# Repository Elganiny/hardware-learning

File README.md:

# Hardware learning log: PCB design with KiCad

Small boards I design while teaching myself electronics and PCB design in **KiCad 10**, with robotics in mind. Each project uses only what I had learned at that point, and the next one builds on it, so the repo shows the progress from my first schematic to complete microcontroller boards.

Every project folder has the KiCad files, a PDF of the schematic, 3D renders, a BOM, the automatic check results and a README that explains **what I decided and why**.

## Projects

| # | Project | What's new in it | Status | |
|---|---|---|---|---|
| P00 | [Mini-Dashboard V1](projects/P00-mini-dashboard-v1/) | first schematic and PCB: LED with series resistor, button with pull-up, JST connector, GND zone | designed, ERC/DRC clean |  |
| P01 | [Mini-Dashboard V2](projects/P01-mini-dashboard-v2/) | its own power supply: micro-USB 5 V → NCP1117 linear regulator → 3.3 V, heat calculation, decoupling placement | designed, ERC/DRC clean |  |
| P02 | Mini-Dashboard V3 (planned) | its own RP2040 microcontroller: flash, crystal, USB data | planned | |

"Designed" means schematic and PCB are finished and pass KiCad's checks. Boards that were manufactured and tested will say so, with measurements.

Units without their own board are written up in the [learning log](learning-log/).

## How I work

1. Learn one topic from a complete, documented design (currently Raspberry Pi's *Hardware design with RP2040*).
2. Design a small board that uses it, following a fixed order of work with checks between the steps: schematic → ERC and reading the netlist → footprints → board outline and connectors → placement → net classes → routing → DRC with schematic parity → labels.
3. Review it against a checklist and write down what I would do differently. Those lessons are in each project's README and CHANGELOG.

## Repository layout

```
projects/<Pnn-name>/
  kicad/      KiCad 10 project (.kicad_pro, .kicad_sch, .kicad_pcb)
  docs/       schematic.pdf, pcb_top.png, pcb_bottom.png, bom.csv, checks.md (generated)
  README.md   what, why, design decisions, status, known issues, test plan
  CHANGELOG.md
templates/    README and CHANGELOG templates for new projects
tools/        update_docs.py: copies the latest KiCad files in and regenerates docs/
```

Regenerate the docs after a change (needs KiCad 10 installed):

```
python tools/update_docs.py
```

## Licence

Copyright 2026 Mohammed Elganayni.

The hardware designs in this repository are licensed under the **CERN Open Hardware Licence Version 2 – Permissive** (SPDX: `CERN-OHL-P-2.0`), see [LICENSE](LICENSE). You may use, modify, manufacture and distribute them; please keep the copyright and licence notice.

KiCad's standard symbol and footprint libraries and the manufacturers' datasheets referenced here have their own terms.

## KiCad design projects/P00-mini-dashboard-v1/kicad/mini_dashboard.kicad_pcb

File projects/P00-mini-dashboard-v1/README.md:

# P00 · Mini-Dashboard V1

My first schematic and PCB: a tiny board with a **power LED** and a **push button**, connected to a microcontroller board by a 3-pin JST PH cable. The microcontroller board supplies the 3.3 V.

| Top | Bottom |
|---|---|
|  |  |

| | |
|---|---|
| Board | 25 × 20 mm, 2 copper layers, parts on top |
| Parts | 5 (LED, 2 resistors, button, connector) |
| Checks | see [docs/checks.md](docs/checks.md): ERC 0 / 0, DRC 0 / 0 with schematic parity |
| Files | [schematic PDF](docs/schematic.pdf) · [BOM](docs/bom.csv) · [KiCad project](kicad/) |
| Status | designed, **not manufactured, not tested** |

## Interface

| J1 pin (JST PH, 2.0 mm) | Signal | Direction |
|---|---|---|
| 1 | GND | — |
| 2 | +3.3 V | in, from the MCU board |
| 3 | BTN | out: 3.3 V = released, 0 V = pressed |

## Design decisions

| Decision | Why |
|---|---|
| **R1 = 270 Ω** in series with a red LED | the LED takes about 2.0 V, the resistor the remaining 1.3 V: I = 1.3 V / 270 Ω ≈ **4.8 mA**, enough for an indicator. Resistor power 6.3 mW |
| **Button to GND with a 10 kΩ pull-up (R2) on the board** | released → R2 pulls BTN to 3.3 V, pressed → 0 V. On the board so it works with any MCU, even if the firmware forgets its internal pull-up. Current while pressed: 0.33 mA |
| **No 100 nF capacitor** | there is no chip on the board, so nothing draws fast current bursts |
| **0603 SMD parts, 6 mm through-hole button** | 0603 is still comfortable to hand-solder; the through-hole button survives being pressed |
| **PWR_FLAG on +3.3 V and GND** | power enters through the connector's passive pins, so ERC needs to be told the nets are powered from outside |
| **GND zone on the bottom layer** | through-hole GND pads connect to it directly; less routing |
| **Trace between the button's two pads "1"** | the button connects them internally, but KiCad's DRC treats them as separate pads |

## Known issues / what I'd do differently

- Traces are long (about 100 mm in total) because I routed before the placement was final.
- All traces are 0.2 mm; power traces should be wider by habit (V2 uses net widths of 0.4 mm).
- No mounting holes, no labels for the connector pins, no board name or version on the silkscreen.
- Values are partly the symbol's placeholders (`LED`, `SW_Push`), so the BOM doesn't say exactly what to order.

These were addressed in [P01](../P01-mini-dashboard-v2/) where possible.

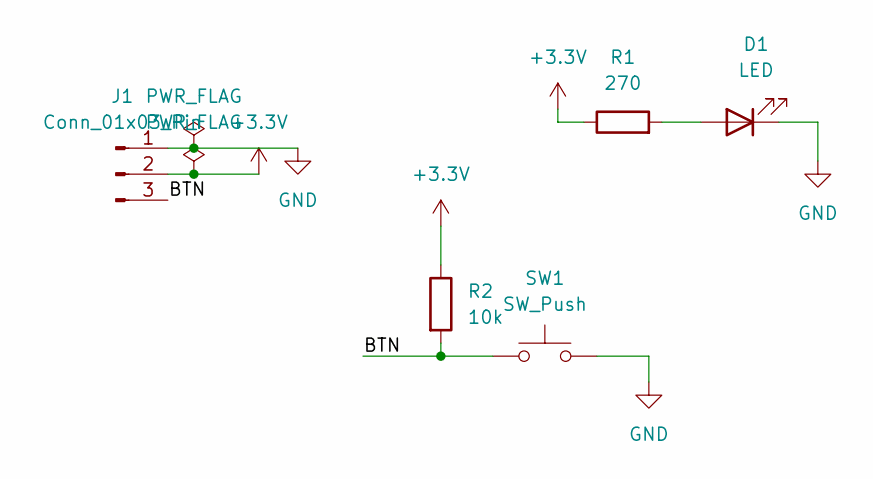
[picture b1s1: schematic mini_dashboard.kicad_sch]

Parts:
D1: LED; LED_0603_1608Metric
J1: Conn_01x03_Pin; JST_PH_B3B-PH-K_1x03_P2.00mm_Vertical
R1: 270; R_0603_1608Metric
R2: 10k; R_0603_1608Metric
SW1: SW_Push; SW_PUSH_6mm

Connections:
+3.3V: J1.2, R1.1, R2.1
/BTN: J1.3, R2.2, SW1.1
GND: D1.1 (K), J1.1, SW1.2
unnamed: D1.2 (A), R1.2

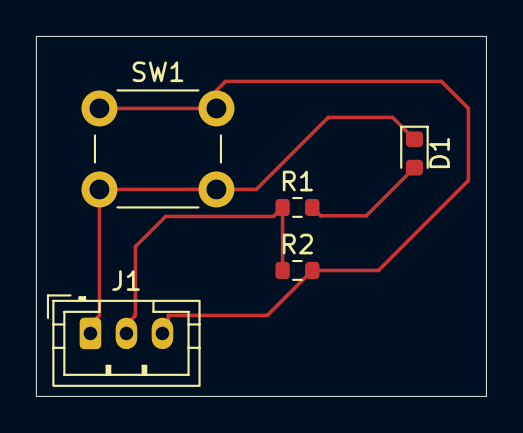
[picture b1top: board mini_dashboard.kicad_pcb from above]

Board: 2 copper layers, 25.0 x 20.0 mm, 5 parts (0 on the bottom side), 4 nets.

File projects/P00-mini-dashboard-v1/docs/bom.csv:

"Refs","Value","Footprint","Qty","DNP"
"D1","LED","LED_SMD:LED_0603_1608Metric","1",""
"J1","Conn_01x03_Pin","Connector_JST:JST_PH_B3B-PH-K_1x03_P2.00mm_Vertical","1",""
"R1","270","Resistor_SMD:R_0603_1608Metric","1",""
"R2","10k","Resistor_SMD:R_0603_1608Metric","1",""
"SW1","SW_Push","Button_Switch_THT:SW_PUSH_6mm","1",""

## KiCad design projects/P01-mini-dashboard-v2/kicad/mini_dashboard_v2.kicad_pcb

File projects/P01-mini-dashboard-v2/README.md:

# P01 · Mini-Dashboard V2: its own power supply

V1 needed 3.3 V from another board. **V2 makes its own 3.3 V from USB**: a micro-USB socket brings 5 V, an NCP1117 linear regulator turns it into 3.3 V, and the LED and button from V1 stay. Plug it into any USB charger and the LED shows that the regulator works.

| Top | Bottom |
|---|---|
|  |  |

| | |
|---|---|
| Board | 25 × 23 mm, 2 copper layers, parts on top |
| Parts | 9 (regulator, 2 capacitors, LED, 2 resistors, button, 2 connectors) |
| Checks | see [docs/checks.md](docs/checks.md): ERC 0 / 0, DRC 0 / 0 with schematic parity |
| Files | [schematic PDF](docs/schematic.pdf) · [BOM](docs/bom.csv) · [KiCad project](kicad/) |
| Status | designed, **not manufactured, not tested** |

## Interfaces

| Connector | Pin | Signal | Note |
|---|---|---|---|
| J2 micro-USB (Amphenol 10118194-0001LF) | VBUS | 5 V in | power only |
| | D+, D−, ID | — | not connected (no USB data on this board) |
| | GND, shield | GND | |
| J1 JST PH, 2.0 mm | 1 | GND | |
| | 2 | **+3.3 V out**, max 100 mA | the other board must not have its own 3.3 V regulator on this pin |
| | 3 | BTN | 3.3 V released, 0 V pressed |

## Design decisions

| Decision | Why |
|---|---|
| **NCP1117 3.3 V linear regulator** | simple, needs only two capacitors. Its dropout is at most 1.10 V at 100 mA, so it needs ≥ 4.4 V in; USB gives 5 V |
| **10 µF 16 V X5R (0805) on the input and output** | the datasheet uses 10 µF in and out; the output capacitor is part of the regulator's control loop and keeps it stable. 16 V is more than 3× the 5 V it sees |
| **Heat check** | the board draws about 5 mA: (5.0 − 3.3) V × 5 mA = 9 mW → +1.4 °C at 160 °C/W. With the full 100 mA on J1 pin 2: 0.17 W → +27 °C, still fine |
| **No PWR_FLAG** | KiCad's micro-USB symbol marks VBUS and GND as *power output* pins, and the regulator output is one too, so ERC already sees a source on every power net |
| **USB data pins marked "no connect"** | power only for now; USB data comes with the microcontroller in V3 |
| **Footprint 10118194 instead of 10103594** | its pads (1–5 + shield) match the symbol one-to-one; the other footprint has extra pads that would have no net |
| **C1 right at the regulator's input pin, C2 right at its output tab** | a regulator's capacitors only work when they are close to its pins |
| **Power traces 0.4 mm, signals 0.25 mm** | the currents are tiny here, but it's the habit needed for boards with motors |
| **GND of the regulator through a via into the bottom GND zone** | short ground path |

## Known issues

- The USB socket's front is about 0.3 mm inside the board edge; it should sit exactly on the edge.
- No mounting holes.
- Some values are still the symbols' placeholders (`LED`, `USB_B_Micro`, `Conn_01x03_Pin`); the schematic has no revision/date yet and no note about J1 pin 2.
- The LED shows that 3.3 V exists, not that USB is plugged in; a second LED on VBUS would tell a dead regulator from a dead cable.

## Test plan (when the board is built)

| Test | Expected | Based on |
|---|---|---|
| VBUS at C1 | 4.75–5.25 V from a USB charger | USB supply |
| +3.3 V at C2 | 3.267–3.333 V (NCP1117, 25 °C) | NCP1117 datasheet |
| Voltage across R1 | about 1.3 V → LED current 4.8 mA | Ohm's law |
| J1 pin 3 | 3.3 V released, 0 V pressed | pull-up R2 |
| U1 temperature after 10 min, LED on | barely above room temperature | heat check above |

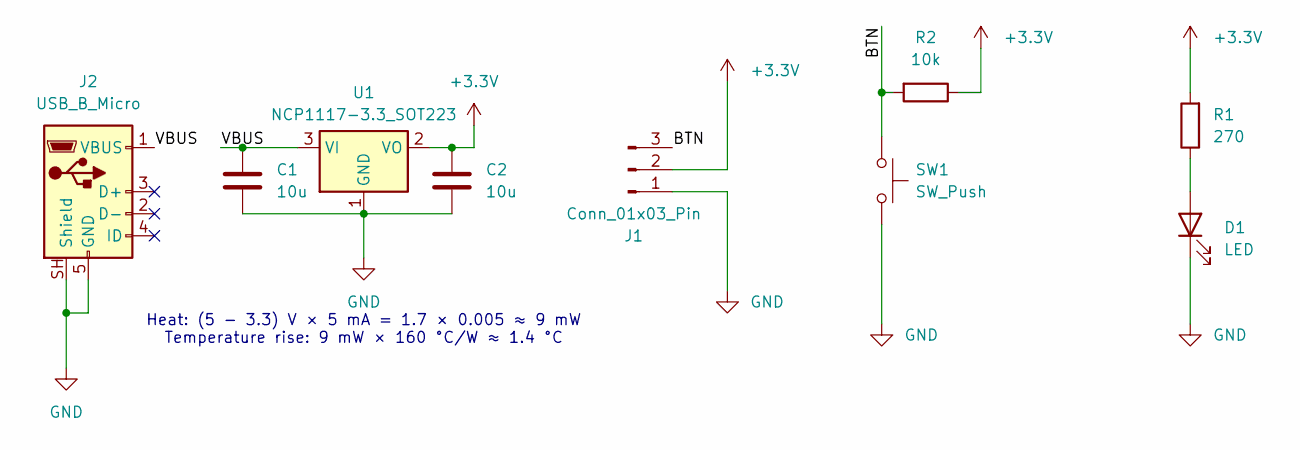
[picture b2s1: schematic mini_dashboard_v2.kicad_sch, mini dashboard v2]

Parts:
C1, C2: 10u; C_0805_2012Metric
D1: LED; LED_0603_1608Metric
J1: Conn_01x03_Pin; JST_PH_B3B-PH-K_1x03_P2.00mm_Vertical
J2: USB_B_Micro; USB_Micro-B_Amphenol_10118194-0001LF_Horizontal
R1: 270; R_0603_1608Metric
R2: 10k; R_0603_1608Metric
SW1: SW_Push; SW_PUSH_6mm
U1: NCP1117-3.3_SOT223; SOT-223-3_TabPin2

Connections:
+3.3V: C2.1, J1.2, R1.2, R2.1, U1.2 (VO)
/BTN: J1.3, R2.2, SW1.1
/VBUS: C1.1, J2.1 (VBUS), U1.3 (VI)
GND: C1.2, C2.2, D1.1 (K), J1.1, J2.5 (GND), J2.SH (Shield), SW1.2, U1.1 (GND)
unnamed: D1.2 (A), R1.1

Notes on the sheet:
Heat: (5 − 3.3) V × 5 mA = 1.7 × 0.005 ≈ 9 mW Temperature rise: 9 mW × 160 °C/W ≈ 1.4 °C

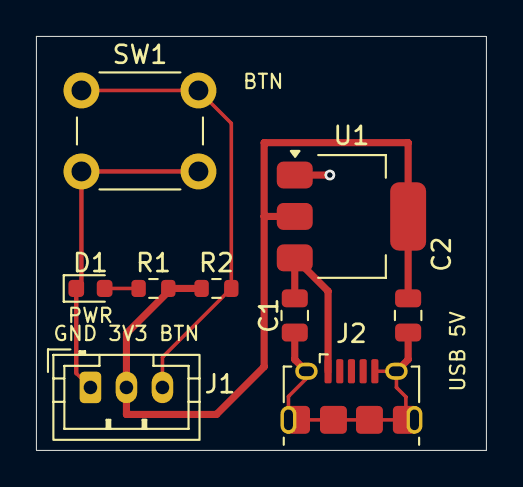
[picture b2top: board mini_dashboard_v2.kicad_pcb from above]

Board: 2 copper layers, 25.0 x 23.0 mm, 9 parts (0 on the bottom side), 5 nets.

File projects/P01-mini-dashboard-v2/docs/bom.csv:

"Refs","Value","Footprint","Qty","DNP"
"C1","10u","Capacitor_SMD:C_0805_2012Metric","1",""
"C2","10u","Capacitor_SMD:C_0805_2012Metric","1",""
"D1","LED","LED_SMD:LED_0603_1608Metric","1",""
"J1","Conn_01x03_Pin","Connector_JST:JST_PH_B3B-PH-K_1x03_P2.00mm_Vertical","1",""
"J2","USB_B_Micro","Connector_USB:USB_Micro-B_Amphenol_10118194-0001LF_Horizontal","1",""
"R1","270","Resistor_SMD:R_0603_1608Metric","1",""
"R2","10k","Resistor_SMD:R_0603_1608Metric","1",""
"SW1","SW_Push","Button_Switch_THT:SW_PUSH_6mm","1",""
"U1","NCP1117-3.3_SOT223","Package_TO_SOT_SMD:SOT-223-3_TabPin2","1",""
